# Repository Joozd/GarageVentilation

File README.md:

# GarageVentilation

**Battery-powered, humidity-aware garage ventilation using an ESP32-C5, Bluetooth sensors and a 5 V fan.**

GarageVentilation is a small DIY project that decides **when ventilating a garage will actually help remove moisture**. Instead of switching a fan on whenever the relative humidity is high, it compares the **absolute humidity** of the air inside and outside. The fan should run only when the garage is humid enough *and* the outside air contains sufficiently less water vapor.

The project combines an ESP32-C5, two existing Bluetooth sensors, a MOSFET-switched fan, and a rechargeable battery. It is being developed with PlatformIO and includes a custom PCB designed in KiCad.

> **Status: work in progress.** BLE measurement decoding, ventilation decision logic, fan switching and sleep behavior are being developed and tested. This is a prototype, not a finished commercial device.

## How it works

```text
    SwitchBot (inside) ── BLE ──┐
                               │
                               ▼
                         ESP32-C5
                               ▲
                               │
    RuuviTag (outside) ── BLE ─┘
                               │
                     Compare humidity
                               │
                   Ventilation worthwhile?
                         /           \
                       yes            no
                        │              │
                   MOSFET → fan     Deep sleep
                        │
                    Light sleep
                        │
                  Measure again
```

1. Scan Bluetooth advertisements from the **indoor SwitchBot** and **outdoor RuuviTag**.
2. Decode temperature and relative humidity from both sensors.
3. Calculate absolute humidity in g/m³.
4. Start the fan if the indoor relative humidity is high enough and the indoor air contains sufficiently more moisture than the outside air.
5. Use different start/continue thresholds (*hysteresis*) to avoid rapidly switching the fan on and off.
6. Sleep between measurements to conserve battery power.

If a measurement cannot be obtained, the controller takes a conservative approach instead of assuming ventilation is useful. While ventilating, the current firmware allows one missed measurement cycle before stopping the fan.

### Why absolute humidity?

Relative humidity alone is misleading when temperatures differ. Cold outside air can have a high relative humidity while containing less water vapor than warmer garage air. Once that outside air warms up in the garage, its relative humidity falls.

Comparing **absolute humidity** gives a better indication of whether exchanging the air will remove moisture. It does not guarantee that every surface will become drier immediately: surface temperature, condensation, airflow and moisture sources still matter.

### Current control thresholds

These are **experimental firmware settings**, not universal recommendations:

| Condition | Start ventilating | Continue ventilating |
| --- | ---: | ---: |
| Minimum indoor relative humidity | 66% | 64% |
| Minimum indoor–outdoor absolute-humidity difference | 2.0 g/m³ | 1.5 g/m³ |

Both conditions must be satisfied. The lower continuation thresholds provide hysteresis.

## Hardware

| Component | Purpose |
| --- | --- |
| Seeed Studio XIAO ESP32-C5 | Microcontroller and BLE receiver |
| SwitchBot temperature/humidity sensor | Indoor measurement via BLE advertisements |
| RuuviTag | Outdoor temperature/humidity measurement via BLE RAWv2 |
| 5 V Noctua fan | Exhaust air from the garage |
| Logic-level N-channel MOSFET | Switch the fan from an ESP32 GPIO |
| Seeed LiPo Rider Plus | Rechargeable battery power and 5 V boost output |
| Single-cell Li-ion battery pack | Portable power source |
| Custom KiCad PCB | Mount and connect the electronics |

### Fan wiring (simplified)

```text
5 V boost output ───────── Fan +
                           Fan − ─── MOSFET drain
ESP32 GPIO (D2) ────────── MOSFET gate
Ground ─────────────────── MOSFET source
```

The ESP32 and fan power supply **must share a common ground**. A suitable gate resistor and gate pull-down are part of the MOSFET control circuit. The fan is switched on the low side; it is **not** powered directly by an ESP32 GPIO.

The ESP32 is powered from the boost converter's 5 V output. Consult the XIAO ESP32-C5 and LiPo Rider Plus documentation before reproducing the power connections, particularly when combining external power and USB.

> **Battery safety:** Use a protected battery pack and a charging/power board appropriate for its chemistry. Check polarity, current limits and mechanical protection before operating unattended.

## Firmware architecture

The code is organized so that measurement collection, humidity decisions, hardware switching and sleep management have separate responsibilities.

```text
main.cpp
  ├── MeasurementsScanner
  │     ├── BleScanner (NimBLE + FreeRTOS queue)
  │     ├── AdvertisementClassifier
  │     ├── RuuviDecoder
  │     └── SwitchbotDecoder
  ├── VentilationController
  ├── Fan
  └── sleep utilities
```

- **`MeasurementsScanner`** gathers and decodes the two sensor measurements. It returns either a complete pair or no measurement.
- **`BleScanner`** handles passive BLE scanning. Incoming advertisements are copied into a bounded FreeRTOS queue and processed by the main application task. Bluetooth is initialized at the start of each scan and deinitialized afterward, so it does not remain active during light sleep.
- **`VentilationController`** decides whether ventilation is worthwhile using measurement data and configurable thresholds; it does not manipulate hardware.
- **`Fan`** owns the output GPIO and controls the MOSFET, including GPIO hold so the output stays high during light sleep.
- **Sleep utilities** put the controller into light sleep while ventilating or deep sleep when ventilation is not needed.

Deep sleep restarts the program on wake-up. Light sleep resumes execution where the program left off.

## Building and flashing

The firmware uses **C++**, the **Arduino framework**, **PlatformIO** and **NimBLE-Arduino**.

1. Install [Visual Studio Code](https://code.visualstudio.com/) and the [PlatformIO IDE extension](https://platformio.org/install/ide?install=vscode).
2. Open this repository as a folder in VS Code.
3. Connect the XIAO ESP32-C5 over USB.
4. In PlatformIO, select the `seeed-xiao-esp32-c5` environment and build/upload the firmware.
5. Open the serial monitor at **115200 baud** for diagnostic output.

The project's `platformio.ini` defines the board, framework and library dependencies. Use the configuration committed with the code rather than copying settings from an older version of this README.

## Power-saving approach

The prototype aims for a low average current draw rather than continuously operating the radio and fan:

- **Fan off:** stop scanning, shut down Bluetooth and enter deep sleep until the next measurement cycle.
- **Fan on:** keep the MOSFET gate asserted, shut down Bluetooth and use light sleep between measurement cycles.
- **After waking:** initialize Bluetooth again for the next scan.

A fan duty cycle around **10%** is an initial design target, not a measured long-term result. Actual battery life depends on fan runtime, battery capacity, boost-converter losses, measurement frequency and standby current. No runtime guarantee is made yet.

## PCB and mechanical design

A custom PCB is designed in **KiCad**. The intent is to keep the electronics easy to assemble and allow the battery to sit in a separate, mechanically secured holder. The LiPo Rider Plus charging connection should remain accessible.

The repository can contain the PCB sources alongside the firmware, for example:

```text
GarageVentilation/
├── src/
├── include/
├── lib/
├── hardware/
│   └── pcb/
│       ├── *.kicad_pro
│       ├── *.kicad_sch
│       └── *.kicad_pcb
├── platformio.ini
└── README.md
```

This layout is illustrative; the actual folder structure may evolve.

## Project status / next steps

- [x] Decode RuuviTag BLE RAWv2 measurements
- [x] Decode SwitchBot temperature/humidity advertisements
- [x] Compare inside/outside absolute humidity
- [x] Drive the fan through a MOSFET
- [x] Test GPIO hold across light sleep
- [x] Design an initial PCB in KiCad
- [ ] Verify reliable repeated BLE scans across sleep cycles
- [ ] Validate long-term power consumption and battery runtime
- [ ] Finish mechanical mounting and battery holder
- [ ] Test control thresholds against real garage conditions
- [ ] Document the finished wiring and add build photos

## A note on scope

This is a purpose-built garage ventilator, not a general home automation platform. The design deliberately favors a small, readable firmware structure and a simple hardware interface over unnecessary abstraction.

---

Built as a practical electronics, embedded C++ and humidity-control learning project.

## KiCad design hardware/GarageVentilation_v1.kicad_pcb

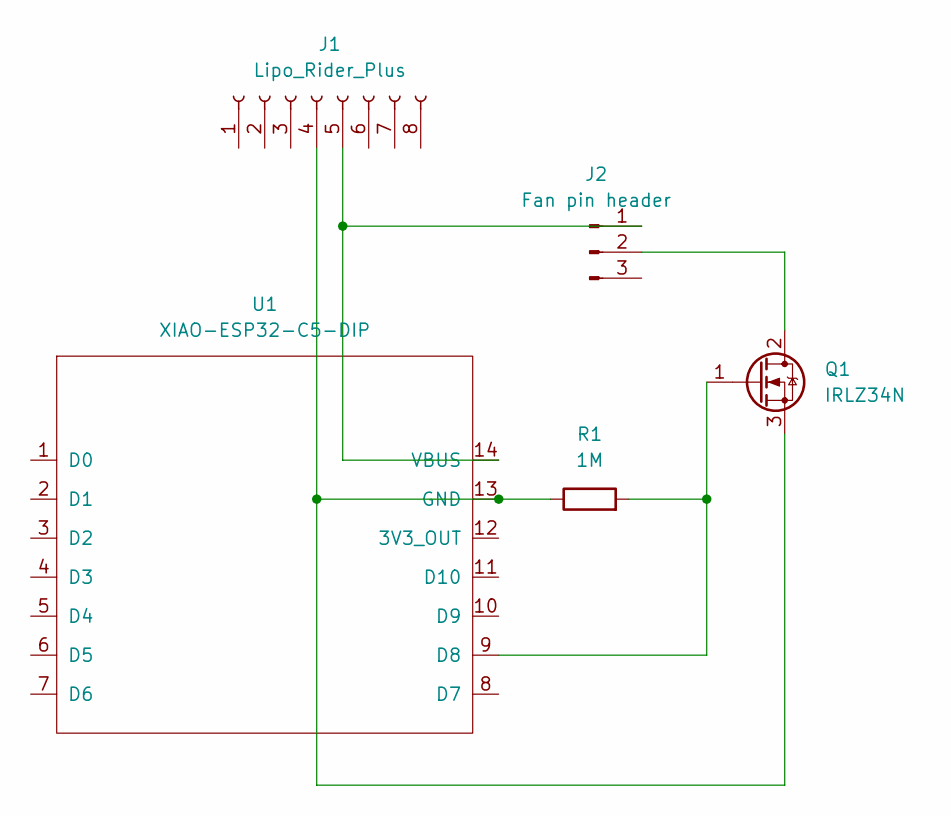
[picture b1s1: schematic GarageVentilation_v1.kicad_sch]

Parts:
J1: Lipo_Rider_Plus; LiPo_Rider_Plus
J2: Fan pin header; FanPinHeader_1x03_P2.54mm_Vertical
Q1: IRLZ34N; TO-220-3_Vertical
R1: 1M; R_Axial_DIN0207_L6.3mm_D2.5mm_P7.62mm_Horizontal
U1: XIAO-ESP32-C5-DIP; XIAO-ESP32-C5-DIP_mount

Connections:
unnamed: J1.5 (5V), J2.1, U1.14 (VBUS)
unnamed: J2.2, Q1.2 (D)
unnamed: Q1.1 (G), R1.2, U1.9 (D8)
unnamed: J1.4 (GND), Q1.3 (S), R1.1, U1.13 (GND)

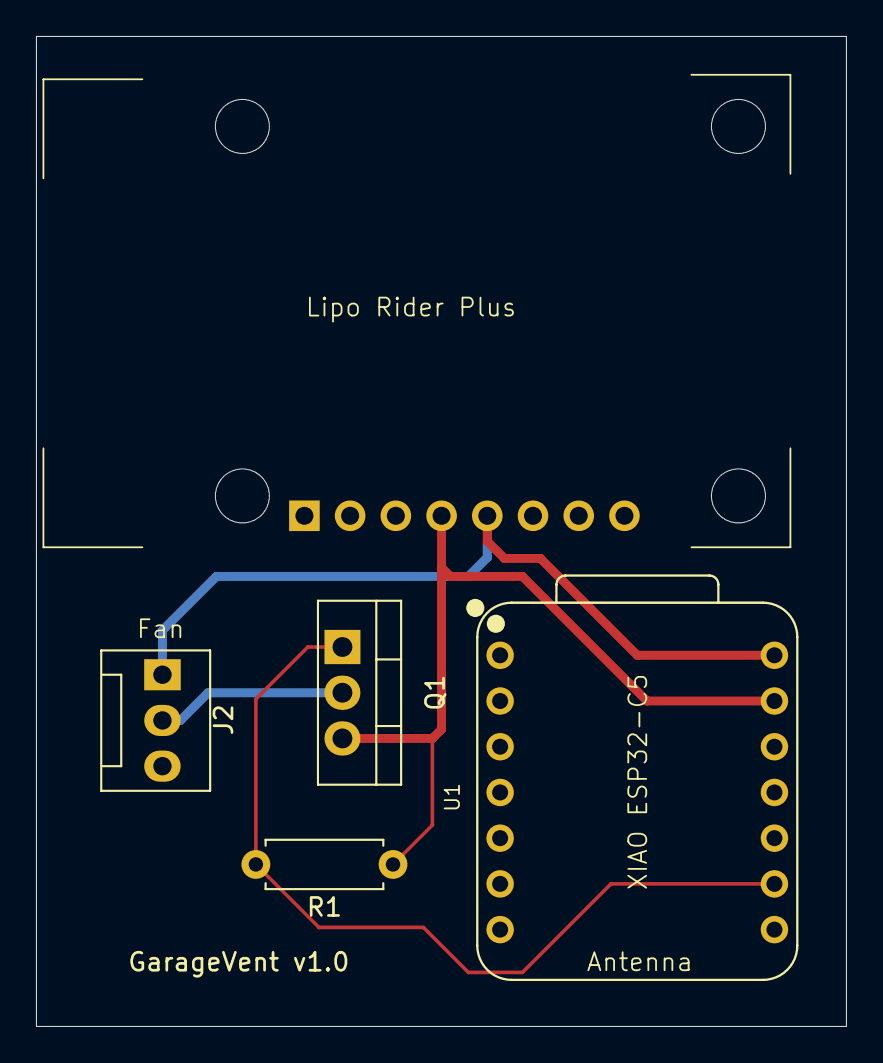
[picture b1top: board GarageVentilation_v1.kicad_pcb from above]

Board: 2 copper layers, 45.0 x 55.0 mm, 5 parts (0 on the bottom side), 4 nets.
